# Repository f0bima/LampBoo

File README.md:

# LampBoo V1
> **KKN UNS JULI-AGUSTUS 2019 POJOK**

## Lampu Bambu Wifi

- Wemos d1 Mini
- Additional Boards Manager URLs : http://arduino.esp8266.com/stable/package_esp8266com_index.json

## Basic Configuration

> **Setting SSID & Project Bucket**

Sambungkan android dengan wifi LampBoo

Setting SSID sesuai dengan wifi yang memiliki akses internet
nama Wifi Rumah dan passwordnya disesuaikan dengan wifi yang tersedia di rumah

> **Setting apk **

download LampBoo APK :https://github.com/f0bima/LampBoo/tree/master/APK

Pastikan Wifi Rumah (wifi dengan akses internet) sudah hidup, jika lampu indikator LampBoo berhenti berkedip berarti LampBoo telah terhubung dengan Wifi Rumah

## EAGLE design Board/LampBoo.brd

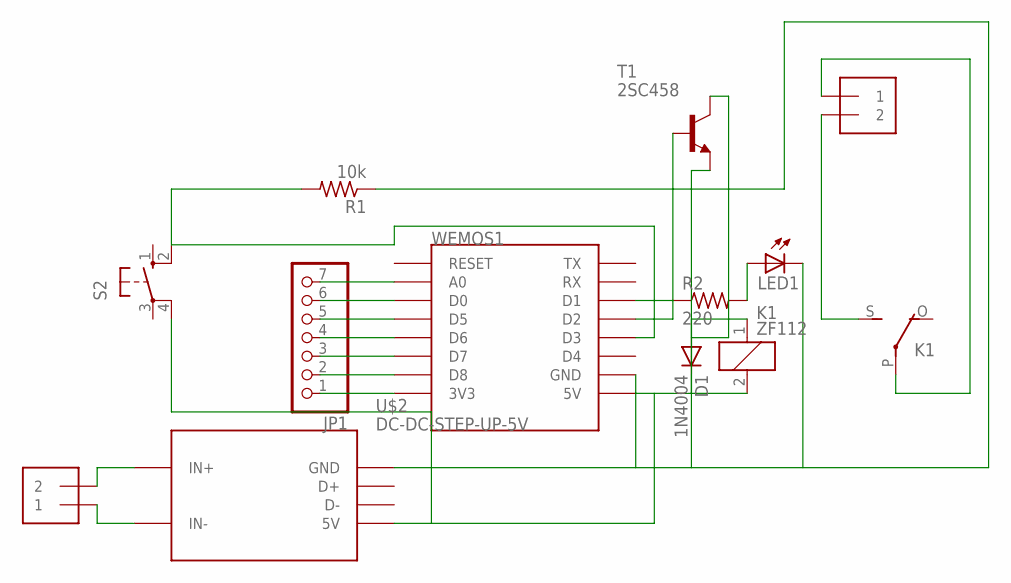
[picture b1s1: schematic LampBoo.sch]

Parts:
D1: 1N4004; DO41-10
J1, J2: 1X2-3.5MM
JP1: PINHD-1X7; 1X07
K1: ZF112
LED1: LED3MM
R1: 10k; 0204/7
R2: 220; 0204/7
S2: 10-XX; B3F-10XX
T1: 2SC458; TO92-ECB
U$2: DC-DC-STEP-UP-5V
WEMOS1: WEMOS-D1-MINI

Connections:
unnamed: D1.C, K1.2, S2.4 (P1), U$2.5V, WEMOS1.5V
unnamed: R2.1, WEMOS1.D2
unnamed: LED1.A, R2.2
unnamed: JP1.1, WEMOS1.3V3
unnamed: JP1.2, WEMOS1.D8
unnamed: J1.2, K1.S
unnamed: J1.1, K1.P
unnamed: LED1.K (C), R1.1, T1.E, U$2.GND, WEMOS1.GND
unnamed: R1.2, S2.2 (S1), WEMOS1.D3
unnamed: J2.2, U$2.IN+
unnamed: J2.1, U$2.IN-
unnamed: JP1.3, WEMOS1.D7
unnamed: JP1.4, WEMOS1.D6
unnamed: JP1.5, WEMOS1.D5
unnamed: JP1.6, WEMOS1.D0
unnamed: JP1.7, WEMOS1.A0
unnamed: D1.A, K1.1, T1.C
unnamed: T1.B, WEMOS1.D1

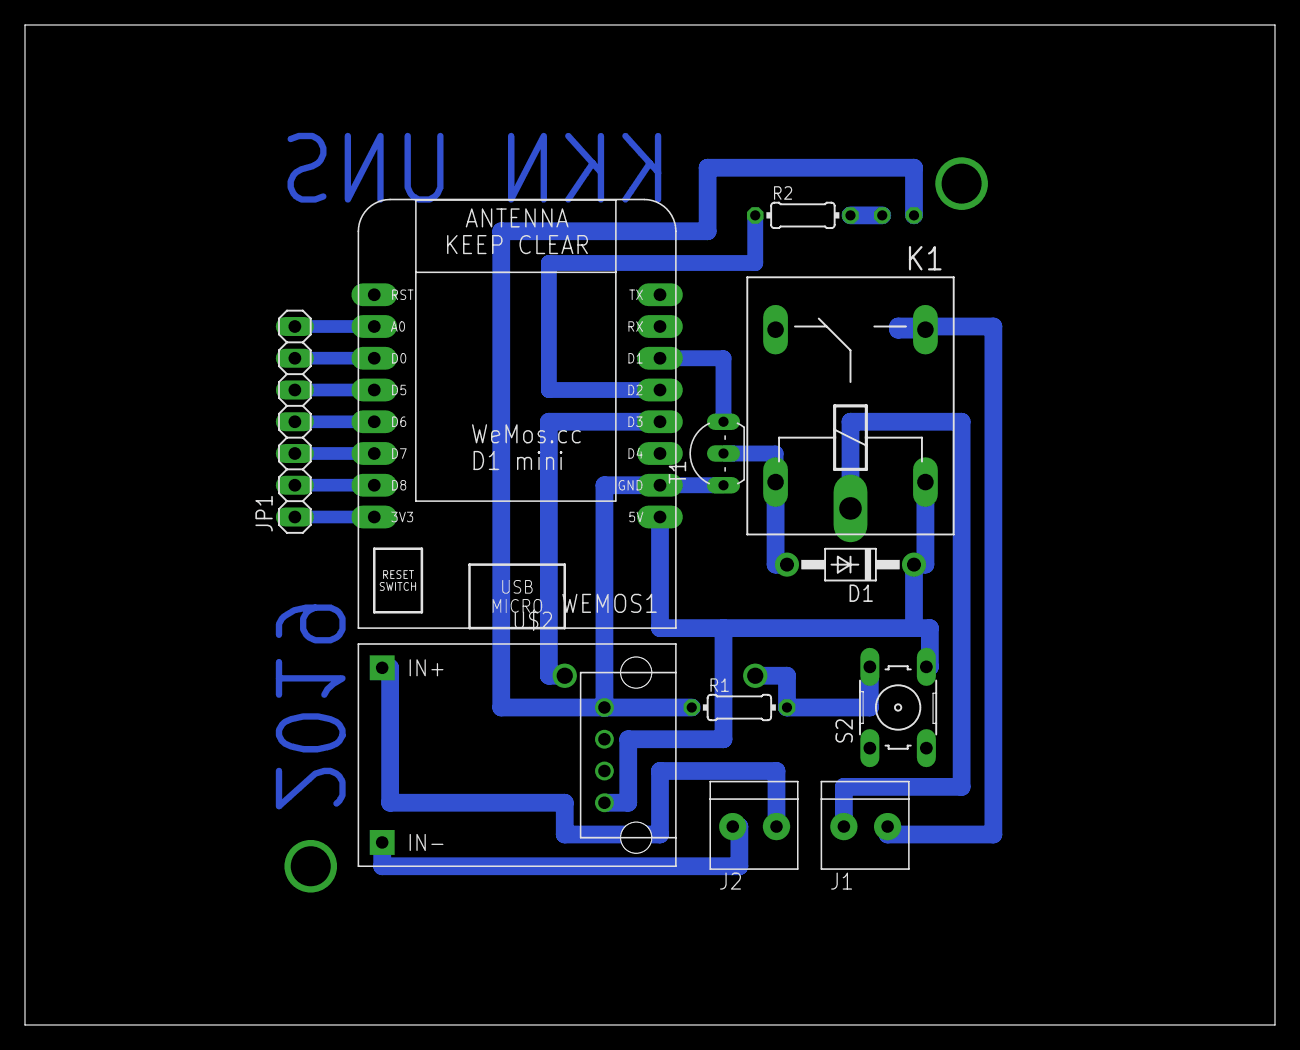
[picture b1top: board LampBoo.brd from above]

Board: 2 copper layers, 100.0 x 80.0 mm, 12 parts (1 on the bottom side), 18 nets.

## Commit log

2019-08-16 LampBoo Arduino
2019-08-16 LampBoo APK

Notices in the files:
parts and their libraries:
diy-modules: Released under the Creative Commons Attribution 4.0 International License: http://creativecommons.org/licenses/by/4.0
